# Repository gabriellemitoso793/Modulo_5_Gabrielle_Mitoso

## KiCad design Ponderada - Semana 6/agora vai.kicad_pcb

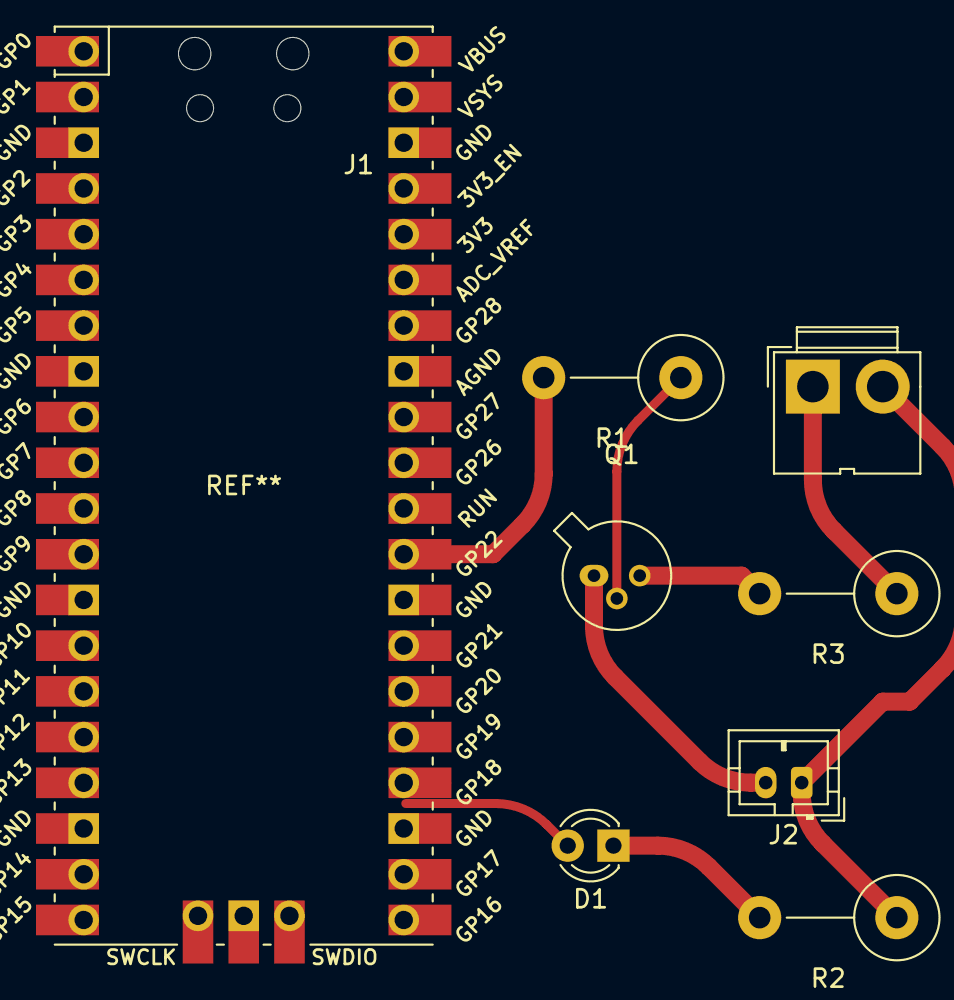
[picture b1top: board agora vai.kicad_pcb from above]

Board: 2 copper layers, 7 parts (0 on the bottom side), 5 nets.

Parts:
D1: LED; LED_D3.0mm
J1: Alimentacao; JWT_A3963_1x02_P3.96mm_Vertical
J2: Conn_01x02_Pin; JST_PH_B2B-PH-K_1x02_P2.00mm_Vertical
Q1: BC108; TO-18-3
R1, R2, R3: R; R_Axial_DIN0414_L11.9mm_D4.5mm_P7.62mm_Vertical

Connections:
GND: J1.2, J2.1, R2.1
unnamed: D1.1 (K), R2.2
unnamed: J2.2, Q1.1 (E), Q1.2 (B), R1.1
unnamed: Q1.3 (C), R3.2
VCC: J1.1, R3.1

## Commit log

2024-02-06 Commit inicial - README.md
2024-02-06 Instalação do Docusaurus
2024-02-06 teste
2024-02-06 Construção da página
2024-02-06 Eliminando pastas
2024-02-08 instalacao do docusaurus
2024-02-16 apagando pastas
2024-02-19 preenchimento de partes
2024-02-19 preenchendo o sobre mim
2024-02-19 git actions
2024-02-19 fix: git actions
2024-02-19 teste git actions
2024-02-19 teste2 git actions
2024-02-29 ponderada braço robotico
2024-02-29 interface grafica e videos
2024-03-28 PONDERADA - SEMANA 6
2024-04-03 ponderada - htmx e flask
2024-04-04 ponderada - semana 7
